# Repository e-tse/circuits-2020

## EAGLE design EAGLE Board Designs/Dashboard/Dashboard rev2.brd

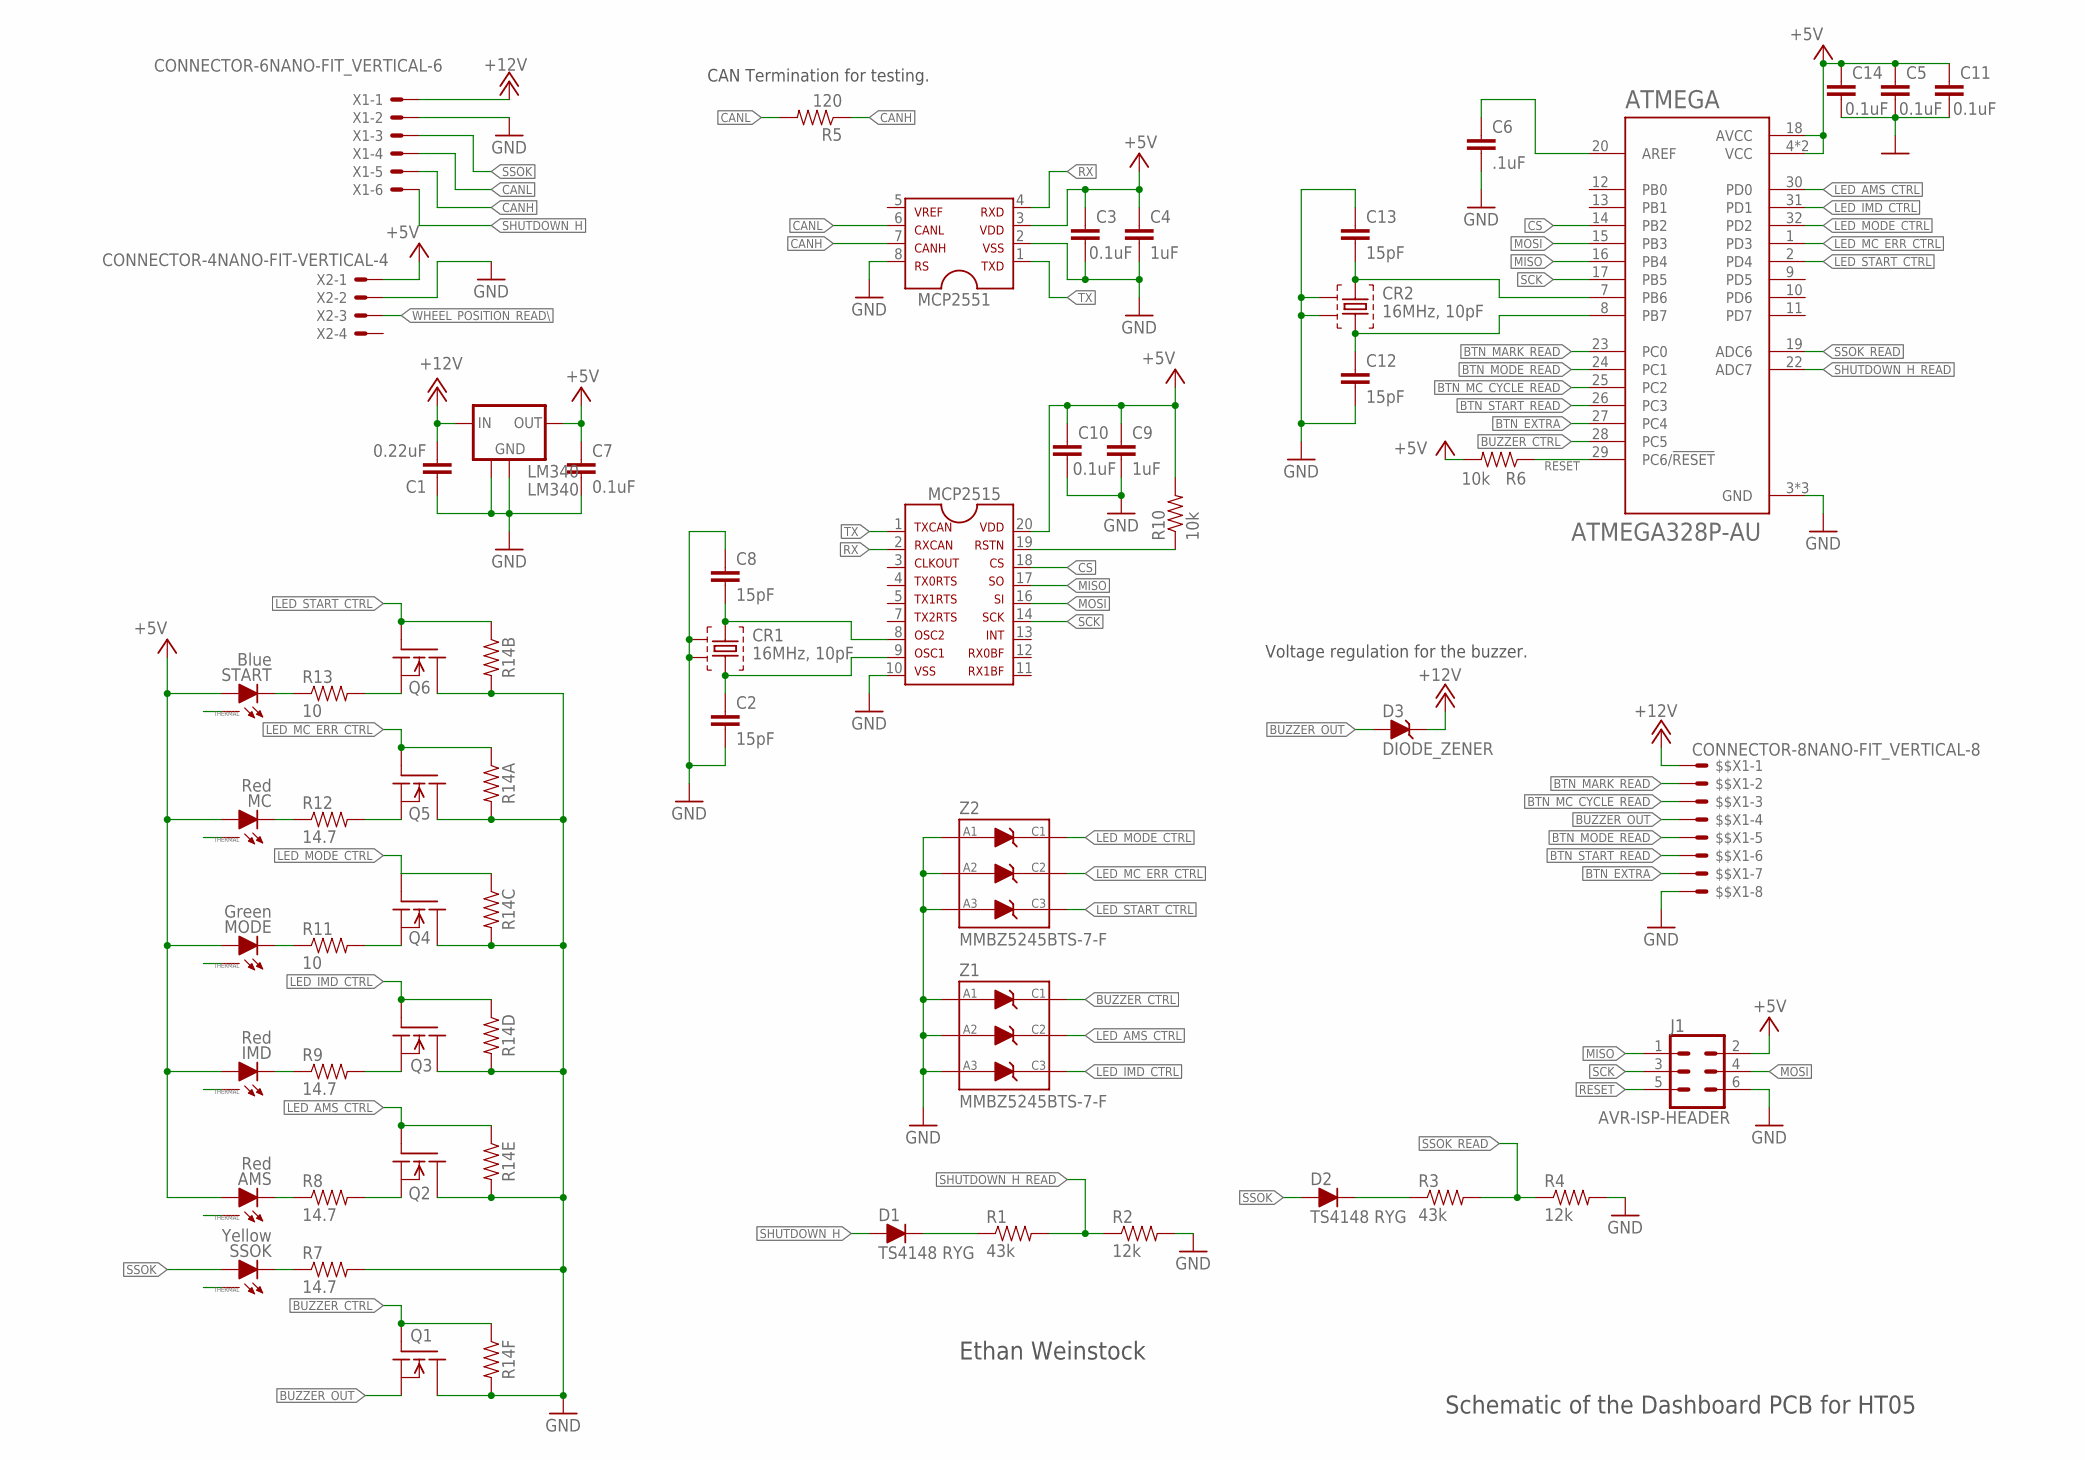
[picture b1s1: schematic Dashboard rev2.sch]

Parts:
$$X1: CONNECTOR-8NANO-FIT_VERTICAL-8; NANO-FIT_VERTICAL-8
AMS: Red; XP-E2
ATMEGA: ATMEGA328P-AU; QFP80P900X900X120-32N
C1: 0.22uF; 0603-CAP
C2, C8, C12, C13: 15pF; 0603-CAP
C3, C5, C7, C10, C11, C14: 0.1uF; 0603-CAP
C4, C9: 1uF; 0603-CAP
C6: .1uF; 0603-CAP
CR1, CR2: 16MHz, 10pF; ABM3B
D1, D2: TS4148 RYG; 0805_D
D3: DIODE_ZENER; SOT23
IMD: Red; XP-E2
J1: AVR-ISP-HEADER; 2X03
LM340: LM340; SOT223
MC: Red; XP-E2
MCP2515: MCP2515TSSOP; TSSOP-20
MCP2551: MCP2551; SOIC-08
MODE: Green; XP-E2
Q1, Q2, Q3, Q4, Q5, Q6: DMG3406LSOT; SOT23
R1, R3: 43k; 0603-RES
R2, R4: 12k; 0603-RES
R5: 120; 0603-RES
R6, R10: 10k; 0603-RES
R7, R8, R9, R12: 14.7; 0603-RES
R11, R13: 10; 0603-RES
R14: 10k; YAG_YC248-M
SSOK: Yellow; XP-E2
START: Blue; XP-E2
X1: CONNECTOR-6NANO-FIT_VERTICAL-6; NANO-FIT_VERTICAL-6
X2: CONNECTOR-4NANO-FIT-VERTICAL-4; NANO-FIT_VERTICAL-4
Z1, Z2: MMBZ5245BTS-7-F; SOT363

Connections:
+5V: AMS.A, ATMEGA.4 (VCC), ATMEGA.6 (VCC), ATMEGA.18 (AVCC), C3.1, C4.1, C5.1, C7.1, C9.1, C10.1, C11.1, C14.1, IMD.A, J1.2, LM340.3 (OUT), MC.A, MCP2515.20 (VDD), MCP2551.3, MODE.A, R6.2, R10.2, START.A, X2.P$1
+12V: $$X1.P$1, C1.2, D3.3 (C), LM340.1 (IN), X1.P$1
BTN_EXTRA: $$X1.P$7, ATMEGA.27 (PC4)
BTN_MARK_READ: $$X1.P$2, ATMEGA.23 (PC0)
BTN_MC_CYCLE_READ: $$X1.P$3, ATMEGA.25 (PC2)
BTN_MODE_READ: $$X1.P$5, ATMEGA.24 (PC1)
BTN_START_READ: $$X1.P$6, ATMEGA.26 (PC3)
BUZZER_CTRL: ATMEGA.28 (PC5), Q1.1 (G), R14.6 (1), Z1.P$4 (C1)
BUZZER_OUT: $$X1.P$4, D3.1 (A), Q1.2 (S)
CANH: MCP2551.7, R5.1, X1.P$5
CANL: MCP2551.6, R5.2, X1.P$4
CS: ATMEGA.14 (PB2), MCP2515.18 (CS)
GND: $$X1.P$8, ATMEGA.3 (GND), ATMEGA.5 (GND), ATMEGA.21 (GND), C1.1, C2.2, C3.2, C4.2, C5.2, C6.2, C7.2, C8.1, C9.2, C10.2, C11.2, C12.2, C13.1, C14.2, CR1.P$2 (2), CR1.P$4 (4), CR2.P$2 (2), CR2.P$4 (4), J1.6, LM340.2 (GND), LM340.4 (GND1), MCP2515.10 (VSS), MCP2551.2, MCP2551.8, Q1.3 (D), Q2.3 (D), Q3.3 (D), Q4.3 (D), Q5.3 (D), Q6.3 (D), R2.2, R4.2, R7.2, R14.11 (2), R14.12 (2), R14.13 (2), R14.14 (2), R14.15 (2), R14.16 (2), X1.P$2, X2.P$2, Z1.P$1 (A1), Z1.P$2 (A2), Z1.P$3 (A3), Z2.P$1 (A1), Z2.P$2 (A2), Z2.P$3 (A3)
LED_AMS_CTRL: ATMEGA.30 (PD0), Q2.1 (G), R14.5 (1), Z1.P$5 (C2)
LED_IMD_CTRL: ATMEGA.31 (PD1), Q3.1 (G), R14.4 (1), Z1.P$6 (C3)
LED_MC_ERR_CTRL: ATMEGA.1 (PD3), Q5.1 (G), R14.1, Z2.P$5 (C2)
LED_MODE_CTRL: ATMEGA.32 (PD2), Q4.1 (G), R14.3 (1), Z2.P$4 (C1)
LED_START_CTRL: ATMEGA.2 (PD4), Q6.1 (G), R14.2 (1), Z2.P$6 (C3)
MISO: ATMEGA.16 (PB4), J1.1, MCP2515.17 (SO)
MOSI: ATMEGA.15 (PB3), J1.4, MCP2515.16 (SI)
unnamed: MCP2515.19 (RSTN), R10.1
unnamed: C2.1, CR1.P$3 (3), MCP2515.9 (OSC1)
unnamed: C8.2, CR1.P$1 (1), MCP2515.8 (OSC2)
unnamed: Q6.2 (S), R13.2
unnamed: ATMEGA.7 (PB6), C13.2, CR2.P$1 (1)
unnamed: ATMEGA.8 (PB7), C12.1, CR2.P$3 (3)
unnamed: D2.C, R3.1
unnamed: ATMEGA.20 (AREF), C6.1
unnamed: Q4.2 (S), R11.2
unnamed: MODE.C, R11.1
unnamed: R13.1, START.C
unnamed: Q3.2 (S), R9.2
unnamed: IMD.C, R9.1
unnamed: D1.C, R1.1
unnamed: R7.1, SSOK.C
unnamed: AMS.C, R8.1
unnamed: Q2.2 (S), R8.2
unnamed: Q5.2 (S), R12.2
unnamed: MC.C, R12.1
RESET: ATMEGA.29 (PC6/!RESET), J1.5, R6.1
RX: MCP2515.2 (RXCAN), MCP2551.4
SCK: ATMEGA.17 (PB5), J1.3, MCP2515.14 (SCK)
SHUTDOWN_H: D1.A, X1.P$6
SHUTDOWN_H_READ: ATMEGA.22 (ADC7), R1.2, R2.1
SSOK: D2.A, SSOK.A, X1.P$3
SSOK_READ: ATMEGA.19 (ADC6), R3.2, R4.1
THERMAL: AMS.X, IMD.X, MC.X, MODE.X, SSOK.X, START.X
TX: MCP2515.1 (TXCAN), MCP2551.1
WHEEL_POSITION_READ\: X2.P$3

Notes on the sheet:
Ethan Weinstock
Schematic of the Dashboard PCB for HT05
Voltage regulation for the buzzer.
CAN Termination for testing.

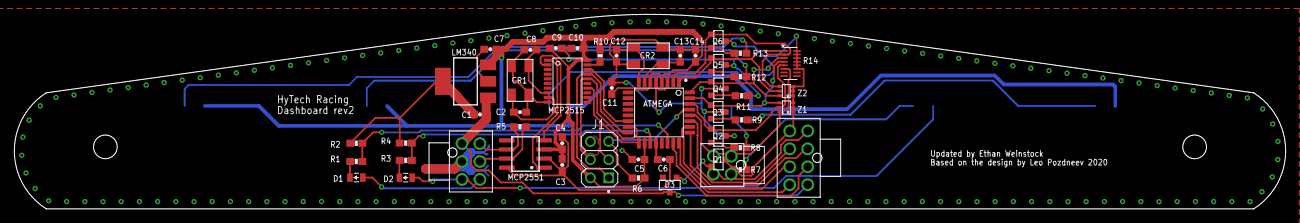
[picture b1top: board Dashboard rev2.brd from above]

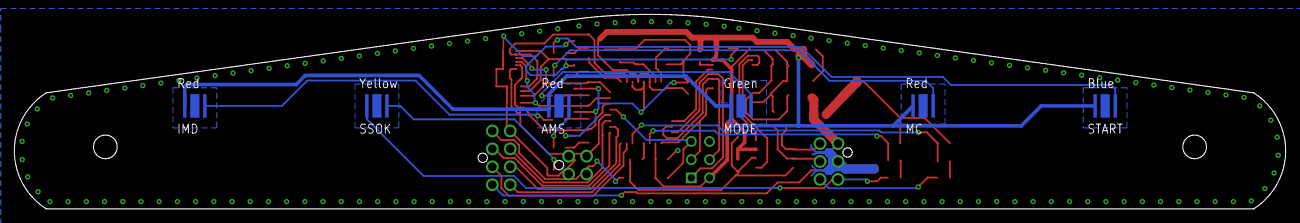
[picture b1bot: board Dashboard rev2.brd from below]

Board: 2 copper layers, 177.4 x 27.1 mm, 55 parts (6 on the bottom side), 48 nets.

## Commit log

2020-09-02 Added 4 pin conector
